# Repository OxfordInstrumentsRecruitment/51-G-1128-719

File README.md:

# 51-G-1128-719
STM32F103 breakout board

This breakout board for the STM32F103 processor provides the following features:
* Compatible with the STM32duino framework
* A USB bootloader, allowing code to be loaded from the Arduino IDE
* A position for a 240x240 RGB screen based on the ST7789 controller
* An SD card reader
* Battery or USB operation
* A three button user interface
* An RGB LED with PWM brightness control
* SPI, UART, I2C, SWD and GPIO external connectivity

# Assembly Instructions

If you were given a blank PCB business card by someone from OI at an event and wish to populate and use it, you will need to follow the instructions in "PCB Business Card Assembly Instructions.PDF", which is in the Documentation folder. If your PCB business card was given to you with components already in place, you can skip this step, and skip programming the USB bootloader.

The assembly instructions document contains a list of the tools and consumables you will need to build this board. For a shopping list of components, check out the file "51-G-1128-719_BOM.xlsx" in the Documentation folder.

The BOM also links each component value to the corresponding reference designator on the PCB.

The display is available from a number of sources. A search for "4-wire SPI interface ST7789 1.3inch 240x240 RGB IPS" will return several listings. At the time of writing, the following listings are available:
* [Ebay from China, cheap but long lead time](https://www.ebay.co.uk/itm/1-3-Inch-Color-IPS-TFT-LCD-Display-Screen-Board-for-ST7789-12Pin-4-Line-Port-SPI/352645419739?hash=item521b4e12db:g:ykQAAOSwu3RcuYoa)
* [Another Ebay listing](https://www.ebay.co.uk/itm/1-3-Inch-Color-IPS-TFT-LCD-Display-Screen-Board-for-ST7789-4-Line-12Pin-SPI-Port/273472845864?hash=item3fac407828:g:eScAAOSwnN9bo0TM&frcectupt=true)
* [And another](https://www.ebay.co.uk/itm/4-wire-SPI-interface-ST7789-1-3inch-240-240Color-IPS-screen-LCD-module-12PIN/173349731176?hash=item285c72fb68:g:XVIAAOSwwhxb-2mn&frcectupt=true)
* [Aliexpress from china, faster postage available](https://www.aliexpress.com/item/1pcs-New-IPS-1-3-inch-3-3V-SPI-interface-HD-Full-Color-TFT-Display-Screen/32904333824.html?spm=2114.search0104.3.9.7f574462Rr9xdn&ws_ab_test=searchweb0_0,searchweb201602_10_10065_10130_10068_10547_319_317_10548_10696_10192_10190_453_10084_454_10083_10618_10307_10820_10301_10821_10303_537_536_10059_10884_10887_321_322_10103,searchweb201603_52,ppcSwitch_0&algo_expid=876473f1-1613-4a7e-939f-4c1f7fcc3143-1&algo_pvid=876473f1-1613-4a7e-939f-4c1f7fcc3143)
* [Another Aliexpress source](https://www.aliexpress.com/item/New-IPS-1-3-inch-3-3V-12PIN-SPI-HD-Full-Color-TFT-Display-Screen-ST7789/32859374478.html?spm=2114.10010108.1000010.4.62b3896di5p0Nv&gps-id=pcDetailLeftTrendProduct&scm=1007.13438.130792.0&scm_id=1007.13438.130792.0&scm-url=1007.13438.130792.0&pvid=27233c3c-7e43-4ec7-a598-0634153de05b)
* [And another](https://www.aliexpress.com/item/New-IPS-1-3-inch-3-3V-12PIN-SPI-HD-Full-Color-TFT-Display-Screen-ST7789/32953548434.html?spm=2114.10010108.1000010.3.62b3896di5p0Nv&gps-id=pcDetailLeftTrendProduct&scm=1007.13438.130792.0&scm_id=1007.13438.130792.0&scm-url=1007.13438.130792.0&pvid=27233c3c-7e43-4ec7-a598-0634153de05b)

# Programming The USB Bootloader

Once you have assembled your PCB business card, you must program the USB bootloader into the STM32F103 in order to use the Arduino IDE to program the device.

This is done using a USB to UART adapter such as the FTDI TTL-232R-3V3 or [equivalent](https://www.ebay.co.uk/sch/i.html?_from=R40&_trksid=m570.l1313&_nkw=usb+to+ttl+uart&_sacat=0). Follow these steps in order to program the bootloader:

* There is a solderable link near the SD card socket labelled "BOOT 0" - apply a bead of solder bridging the center to the side marked "1"
* Solder the RX, TX and GND signals from the USB to UART adapter to PA9, PA10 and GND on the PCB business card. PA9 and PA10 can be accessed via the GPIO pins on the right hand side of the PCB. When using an FTDI USB to UART cable, the orange wire goes to PA10 and the yellow wire goes to PA9.
* The exact programming procedure is slightly different on Windows, Linux and Mac. A Windows utility is provided to program the PCB in the Firmware\Bootloader\stm32tools\2019.2.28\win\ folder. The utility is called stm32flash.exe and runs stand alone with no installation required. The bootloader binary is "generic_boot20_pb9.bin" and can be found under the folder Firmware\Bootloader\. To use the provided utility on widnows:
  * Open a CMD window and navigate to Firmware\Bootloader\
  * Connect the USB to UART adapter and apply power to the PCB business card.
  * Determine the COM port number of the USB to UART adapter (this can be done from the Arduino IDE, or by opening device manager)
  * Then run the command (replacing the 3 in "COM3" with the COM port number on your system):
  `stm32tools\2019.2.28\win\stm32flash.exe -w generic_boot20_pb9.bin -v -g 0x0 COM3`
* If you are running Linux or Mac, follow the instructions on [this page of the STM32duino wiki](http://wiki.stm32duino.com/index.php?title=Burning_the_bootloader)
* Once the bootloader is programmed, remove power from the PCB business card and solder the "BOOT 0" link into the "0" position

# Uploading Your First Sketch

The PCB business card USB bootloader uses the standard windows DFU (Device Firmware Upload) driver, however the USB VID and PID are not known to Windows and therefore Windows will say "USB device not recognised" when you connect it. This problem can be solved by running the script "install_drivers.bat" in the folder: Firmware\drivers\win\

Once this is done, Windows should enumerate the PCB business card as a DFU capable device. This step is not required on Mac or Linux as both operating systems recognize the device as DFU capable and do not care about the VID and PID.

To program the example sketch onto the PCB card, follow these steps:

* Install the Arduino IDE
* Follow the instructions on [this page](http://wiki.stm32duino.com/index.php?title=Installation) to install the STM32duino extensions for the Arduino IDE
* copy the folders from Firmware\Libs\ into your Arduino Libraries folder.
* start the Arduino IDE (note that the IDE must not be open when you copy the library folders)
* open Firmware\Test\graphicstest\graphicstest.ino
* Select the correct COM port from the tools menu in the Arduino IDE
* Press the upload button

This sketch will display some test graphics. If you have an SD card, copy the contents of Firmware\Test\SD_Graphics\ onto it and put the SD card in the PCD business card. The card will now display some images from the card. The name on the name tag display comes from the file name.txt on the SD card. The logo on the same page comes from logo.bmp. The name must not be more than 13 characters. The job title must not be more than 20 characters. the logo must be 240 pixels wide and in uncompressed 24-bit bitmap format.

Up to 255 images can be added to the SD card with number names from 1.bmp to 255.bmp. Each will be displayed for 2 seconds.

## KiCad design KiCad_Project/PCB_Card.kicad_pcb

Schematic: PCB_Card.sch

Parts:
BT1: Battery; BatteryHolder_Keystone_2479_3xAAA
C1, C2: 1uF; C_0805_2012Metric_Pad1.15x1.40mm_HandSolder
C3, C4, C5, C6, C9, C10, C11: 100nF; C_0805_2012Metric_Pad1.15x1.40mm_HandSolder
C7, C8: 18pF; C_0805_2012Metric_Pad1.15x1.40mm_HandSolder
D1: GREEN; LED_0805_2012Metric_Pad1.15x1.40mm_HandSolder
D2: LED_RGB; LED_RGB_1210
J1: USB_B_Micro; USB_Micro-B_Molex_47346-0001
J2: EXT_SPI; PinHeader_1x06_P2.54mm_Horizontal
J3: GPIO; PinHeader_1x06_P2.54mm_Horizontal
J4: EXT_I2C; PinHeader_1x04_P2.54mm_Horizontal
J5: EXT_UART; PinHeader_1x06_P2.54mm_Horizontal
J6: Conn_01x12_Female; 1.3_240x240_RGB_IPS_LCD
J9: SWD; PinHeader_1x05_P2.54mm_Horizontal
J10: SD_Card; microSD_HC_Hirose_DM3AT-SF-PEJM5
JP1: BOOT0; SolderJumper-3_P1.3mm_Open_RoundedPad1.0x1.5mm
JP2: BOOT1; SolderJumper-3_P1.3mm_Bridged12_RoundedPad1.0x1.5mm
JP3, JP4, JP5: Voltage Select; SolderJumper-3_P1.3mm_Bridged12_RoundedPad1.0x1.5mm
JP6: Jumper; SolderJumper-2_P1.3mm_Open_RoundedPad1.0x1.5mm
Q1: BC817DS; SOT-23-6_Handsoldering
R1, R9, R15: 1K5; R_0805_2012Metric_Pad1.15x1.40mm_HandSolder
R2, R3, R7, R11, R16, R17: 33K; R_0805_2012Metric_Pad1.15x1.40mm_HandSolder
R4: 22R; R_0805_2012Metric_Pad1.15x1.40mm_HandSolder
R5: 120R; R_0805_2012Metric_Pad1.15x1.40mm_HandSolder
R6: 16R; R_0805_2012Metric_Pad1.15x1.40mm_HandSolder
R8, R10: 4K7; R_0805_2012Metric_Pad1.15x1.40mm_HandSolder
R14: 6R8; R_0805_2012Metric_Pad1.15x1.40mm_HandSolder
SW1: Power; SW_SPDT_CK-JS102011SAQN
SW2: RESET; SW_SPST_B3SL-1022P
SW3: LEFT; SW_SPST_B3SL-1022P
SW4: ENTER; SW_SPST_B3SL-1022P
SW5: RIGHT; SW_SPST_B3SL-1022P
TP1, TP2, TP3, TP4, TP5, TP6: TestPoint; TestPoint_Pad_D1.0mm
TP7: TestPoint; TestPoint_THTPad_D2.0mm_Drill1.0mm
TP8: +5V; TestPoint_Pad_D3.0mm
TP9: D+; TestPoint_Pad_D1.0mm
TP10: D-; TestPoint_Pad_D1.0mm
U1: STM32F103C8Tx; LQFP-48_7x7mm_P0.5mm
U2: MIC5504-3.3YM5; SOT-23-5_HandSoldering
Y1: 8MHz; Crystal_SMD_Abracon_ABM3-2Pin_5.0x3.2mm_HandSoldering

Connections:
+3V3: C2.1, C3.1, C4.1, C5.1, C6.1, C9.1, C10.1, C11.1, D2.1, J6.4, J9.2, J10.4 (VDD), JP1.3, JP2.3, JP3.1, JP4.1, JP5.1, R7.1, R15.2, R16.1, U1.1, U1.9, U1.24, U1.36, U1.48, U2.5
+5V: C1.1, D1.2, J6.3, JP3.3, JP4.3, JP5.3, JP6.2, R2.1, SW1.2, TP8.1, U2.1, U2.3
BOOT0: JP1.2, R11.1, TP7.1, U1.44
BOOT1: JP2.2, U1.20
EXT_I2C_SCL: J4.3, R8.2, U1.42
EXT_I2C_SDA: J4.4, R10.2, U1.43
EXT_SPI_MISO: J2.5, J10.7 (DAT0), U1.27
EXT_SPI_MOSI: J2.4, J10.3 (CMD), U1.28
EXT_SPI_NSS: J2.6, J10.2 (DAT3/CD), U1.25
EXT_SPI_SCL: J2.3, J10.5 (CLK), U1.26
EXT_UART_CTS: J5.2, U1.10
EXT_UART_RTS: J5.6, U1.11
EXT_UART_RX: J5.5, U1.13
EXT_UART_TX: J5.4, U1.12
GND: BT1.2, C1.2, C2.2, C3.2, C4.2, C5.2, C6.2, C7.2, C8.2, C9.2, C10.2, C11.2, J1.5, J2.1, J4.1, J5.1, J6.1, J6.5, J6.6, J6.12, J9.1, J10.6 (VSS), J10.9 (DET_B), JP1.1, JP2.1, Q1.4, R1.2, R3.2, R11.2, R14.1, R17.1, SW2.1, SW3.1, SW4.1, SW5.1, TP6.1, U1.8, U1.23, U1.35, U1.47, U2.2
GPIO_PA9: J3.3, U1.30
GPIO_PA10: J3.4, U1.31
GPIO_PA15: J3.5, U1.38
GPIO_PB0: J3.6, U1.18
GPIO_PB10: J3.1, U1.21
GPIO_PB11: J3.2, U1.22
LCD_CS: J6.8, TP2.1, U1.14
LCD_DC: J6.7, TP1.1, U1.41
LCD_LED_CTRL: R9.2, U1.29
LCD_MOSI: J6.10, TP4.1, U1.17
LCD_RST: J6.11, TP5.1, U1.40
LCD_SCL: J6.9, TP3.1, U1.15
LED_B: R6.2, U1.19
LED_G: R4.2, U1.45
LED_R: R5.2, U1.46
unnamed: BT1.1, SW1.3
unnamed: D1.1, R1.1
unnamed: D2.2, R5.1
unnamed: D2.3, R4.1
unnamed: D2.4, R6.1
unnamed: J1.1, JP6.1, SW1.1
unnamed: J2.2, JP3.2
unnamed: J4.2, JP4.2, R8.1, R10.1
unnamed: J5.3, JP5.2
unnamed: J6.2, Q1.6
unnamed: Q1.1, Q1.5, R14.2
unnamed: Q1.2, Q1.3, R9.1
OSC_1: C7.1, U1.5, Y1.1
OSC_2: C8.1, U1.6, Y1.2
RESET: J9.5, R7.2, SW2.2, U1.7
SD_DET: J10.10 (DET_A), U1.39
SWCLK: J9.3, R17.2, U1.37
SWDIO: J9.4, R16.2, U1.34
SW_ENTER: SW4.2, U1.4
SW_LEFT: SW3.2, U1.2
SW_RIGHT: SW5.2, U1.3
USB_D+: J1.3, R15.1, TP9.1, U1.33
USB_D-: J1.2, TP10.1, U1.32
VBAT: R2.2, R3.1, U1.16

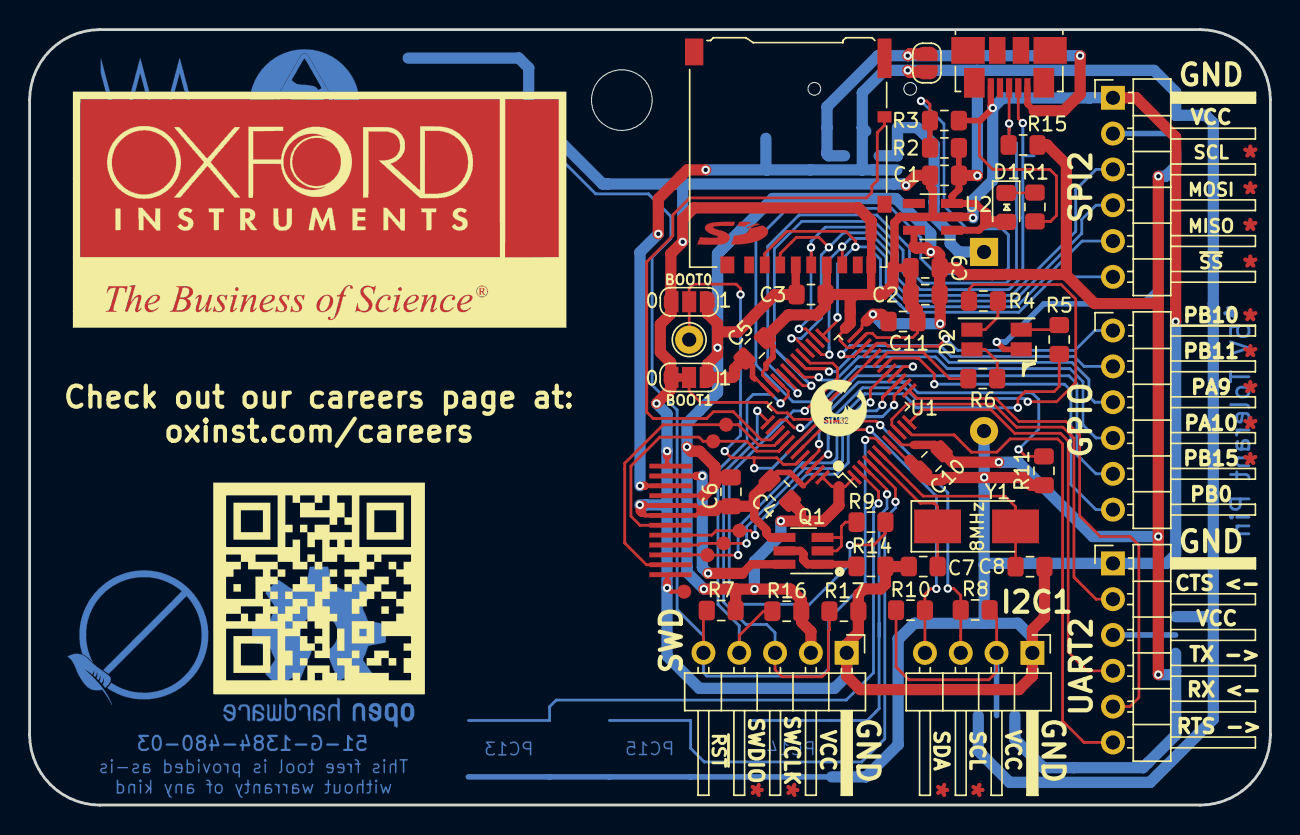
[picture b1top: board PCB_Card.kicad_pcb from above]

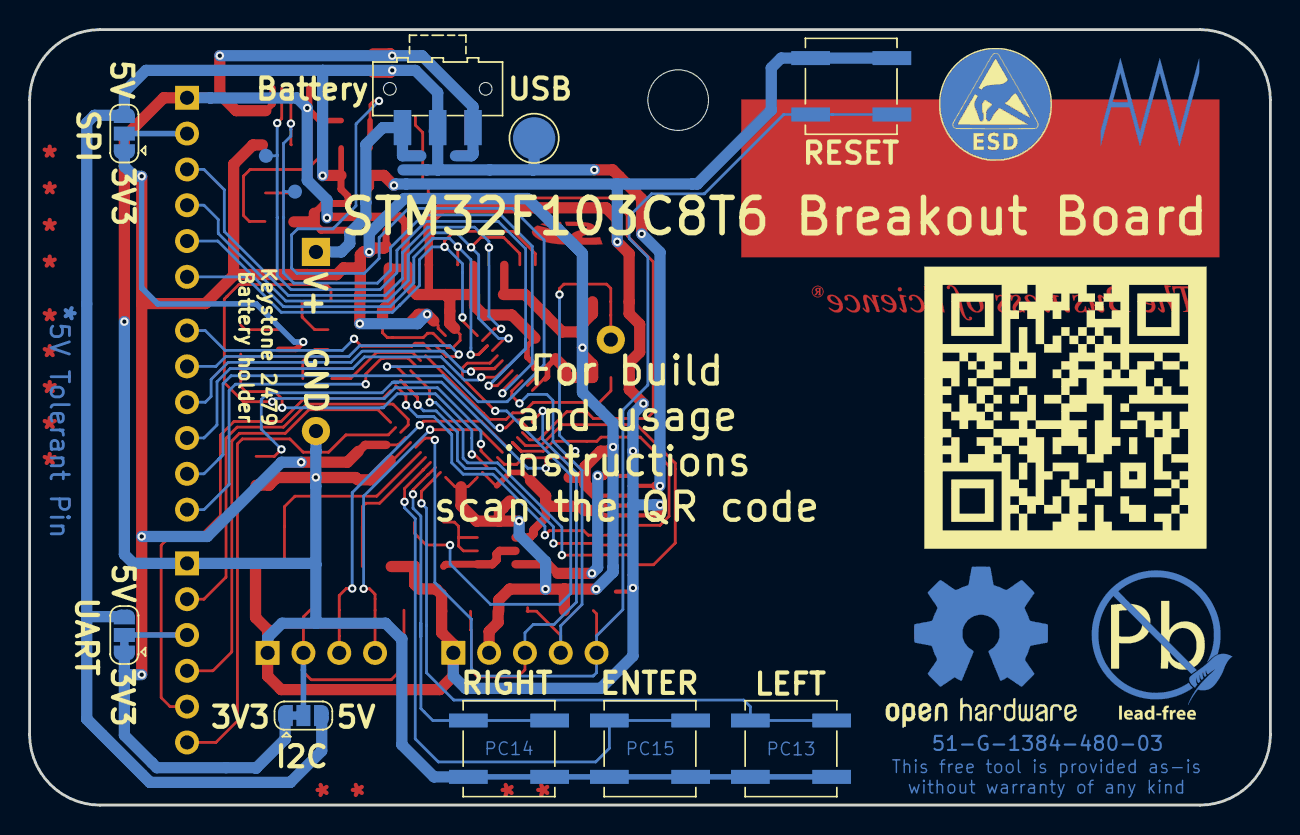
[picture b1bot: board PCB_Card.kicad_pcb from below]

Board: 2 copper layers, 88.0 x 55.0 mm, 62 parts (12 on the bottom side), 54 nets.

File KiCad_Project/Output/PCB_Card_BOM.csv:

"Id";"Designator";"Package";"Quantity";"Designation";"Supplier and ref";
1;"J6";"1.3_240x240_RGB_IPS_LCD";1;"Conn_01x12_Female";;;
2;"G***";"Oxford_Logo_35mm_Mask";1;"LOGO";;;
3;"G***";"Oxford_Logo_35mm_Copper";1;"LOGO";;;
4;"Y1";"Crystal_SMD_Abracon_ABM3-2Pin_5.0x3.2mm_HandSoldering";1;"8MHz";;;
5;"BT1";"BatteryHolder_Keystone_2479_3xAAA";1;"Battery";;;
6;"G***";"SD_Logo_5mm_inv";1;"LOGO";;;
7;"JP1";"SolderJumper-3_P1.3mm_Open_RoundedPad1.0x1.5mm";1;"BOOT0";;;
8;"JP2";"SolderJumper-3_P1.3mm_Bridged12_RoundedPad1.0x1.5mm";1;"BOOT1";;;
9;"C4,C5,C3,C6,C9,C10,C11";"C_0805_2012Metric_Pad1.15x1.40mm_HandSolder";7;"100nF";;;
10;"U1";"LQFP-48_7x7mm_P0.5mm";1;"STM32F103C8Tx";;;
11;"J10";"microSD_HC_Hirose_DM3AT-SF-PEJM5";1;"SD_Card";;;
12;"G***";"ST32_Logo";1;"LOGO";;;
13;"R15,R1,R9";"R_0805_2012Metric_Pad1.15x1.40mm_HandSolder";3;"1K5";;;
14;"SW1";"SW_SPDT_CK-JS102011SAQN";1;"Power";;;
15;"J3";"PinHeader_1x06_P2.54mm_Horizontal";1;"GPIO";;;
16;"C7,C8";"C_0805_2012Metric_Pad1.15x1.40mm_HandSolder";2;"18pF";;;
17;"R8,R10";"R_0805_2012Metric_Pad1.15x1.40mm_HandSolder";2;"4K7";;;
18;"D2";"LED_RGB_1210";1;"LED_RGB";;;
19;"SW4";"SW_SPST_B3SL-1022P";1;"ENTER";;;
20;"C1,C2";"C_0805_2012Metric_Pad1.15x1.40mm_HandSolder";2;"1uF";;;
21;"J1";"USB_Micro-B_Molex_47346-0001";1;"USB_B_Micro";;;
22;"J2";"PinHeader_1x06_P2.54mm_Horizontal";1;"EXT_SPI";;;
23;"J4";"PinHeader_1x04_P2.54mm_Horizontal";1;"EXT_I2C";;;
24;"J5";"PinHeader_1x06_P2.54mm_Horizontal";1;"EXT_UART";;;
25;"JP3,JP4,JP5";"SolderJumper-3_P1.3mm_Bridged12_RoundedPad1.0x1.5mm";3;"Voltage Select";;;
26;"R2,R3,R7,R16,R17,R11";"R_0805_2012Metric_Pad1.15x1.40mm_HandSolder";6;"33K";;;
27;"R4";"R_0805_2012Metric_Pad1.15x1.40mm_HandSolder";1;"22R";;;
28;"R5";"R_0805_2012Metric_Pad1.15x1.40mm_HandSolder";1;"120R";;;
29;"R6";"R_0805_2012Metric_Pad1.15x1.40mm_HandSolder";1;"16R";;;
30;"SW2";"SW_SPST_B3SL-1022P";1;"RESET";;;
31;"SW3";"SW_SPST_B3SL-1022P";1;"LEFT";;;
32;"SW5";"SW_SPST_B3SL-1022P";1;"RIGHT";;;
33;"U2";"SOT-23-5_HandSoldering";1;"MIC5504-3.3YM5";;;
34;"";"MountingHole_4.3mm_M4";1;"MountingHole_4.3mm_M4";;;
35;"G***";"github_link";1;"LOGO";;;
36;"G***";"OI_Careers_link";1;"LOGO";;;
37;"G***";"AW_Signature_7mm_inv";1;"LOGO";;;
38;"G***";"Open_Hardware";1;"LOGO";;;
39;"G***";"PB_Free_Ring";1;"LOGO";;;
40;"G***";"PB_Free_Text";1;"LOGO";;;
41;"J9";"PinHeader_1x05_P2.54mm_Horizontal";1;"SWD";;;
42;"G***";"ESD_Copper_8mm";1;"LOGO";;;
43;"G***";"ESD_Silk_8mm";1;"LOGO";;;
44;"D1";"LED_0805_2012Metric_Pad1.15x1.40mm_HandSolder";1;"GREEN";;;
45;"TP1,TP2,TP3,TP4,TP5,TP6";"TestPoint_Pad_D1.0mm";6;"TestPoint";;;
46;"TP7";"TestPoint_THTPad_D2.0mm_Drill1.0mm";1;"TestPoint";;;
47;"JP6";"SolderJumper-2_P1.3mm_Open_RoundedPad1.0x1.5mm";1;"Jumper";;;
48;"Q1";"SOT-23-6_Handsoldering";1;"BC817DS";;;
49;"R14";"R_0805_2012Metric_Pad1.15x1.40mm_HandSolder";1;"6R8";;;
50;"TP8";"TestPoint_Pad_D3.0mm";1;"+5V";;;
51;"TP9";"TestPoint_Pad_D1.0mm";1;"D+";;;
52;"TP10";"TestPoint_Pad_D1.0mm";1;"D-";;;
53;"G***";"Oxford_Logo_35mm_Silk";1;"LOGO";;;

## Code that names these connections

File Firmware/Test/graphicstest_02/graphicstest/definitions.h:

#ifndef DEFINITIONS
#define DEFINITIONS

//display state machine states
enum
{
  DISPLAYSTATE_NONE,
  DISPLAYSTATE_BLACK,
  DISPLAYSTATE_TAG,
  DISPLAYSTATE_IMAGE,
  DISPLAYSTATE_LORUM,
  DISPLAYSTATE_PRINT,
  DISPLAYSTATE_LINES,
  DISPLAYSTATE_RECT,
  DISPLAYSTATE_FILLRECT,
  DISPLAYSTATE_CIRCLES,
  DISPLAYSTATE_TRIANGLES,
};

//general purpose return states
enum
{
  STATUS_OK,
  STATUS_ERROR,
  STATUS_NOFILE,
  STATUS_NOSD,
  STATUS_FORMATERR,
};

//scheduler states
enum
{
  SCHED_STOPPED,
  SCHED_ARMED,
  SCHED_TRIGGERED,
  SCHED_WAIT,
  SCHED_TAG,
  SCHED_IMG,
  SCHED_PRINT,
  SCHED_LINES,
  SCHED_FILLRECT,
  SCHED_TRIANGLES,
  SCHED_CIRCLES,
};



//pin definitions
#define TFT_CS        PA4
#define TFT_RST       PB4
#define TFT_DC        PB5
#define TFT_BACKLIGHT PA8
#define LED_RED       PB9
#define LED_GREEN     PB8
#define LED_BLUE      PB1
#define SD_DET        PB3
#define SW_LEFT       PC13
#define SW_RIGHT      PC14
#define SW_ENTER      PC15
#define SD_CS         PB12

#define WHEELPOSMAX   767
#define LED_RATE 10000    // in microseconds
#define LCD_DEFAULT_BRIGHTNESS 65535


//------------------------------------------------------------------------------
// print error msg, any SD error codes, and halt.
// store messages in flash
#define errorExit(msg) errorHalt(F(msg))
#define initError(msg) initErrorHalt(F(msg))
//------------------------------------------------------------------------------

#endif

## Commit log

2019-03-01 Added kikad project
2019-03-01 Added manufacturing pack
2019-03-01 Added renders
2019-03-29 Added firmware
2019-03-29 Added documentation
2019-04-02 Updated to latest PCB CAD (revision 3)
2019-04-02 Updated manufacturing pack to latest version (R3)
2019-04-03 Added instructions
2019-05-10 Added software libs
2019-05-10 Updated PCB CAD
    Added 3D CAD of programming jig, screen alignment jig etc
    Added LT spice simulation of LED driver circuit
